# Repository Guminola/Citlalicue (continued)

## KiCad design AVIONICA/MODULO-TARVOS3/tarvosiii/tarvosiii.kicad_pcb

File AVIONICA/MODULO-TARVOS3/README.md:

# Modulo Tarvos-iii
2/3

modulo de comunicaciones Tarvos-iii

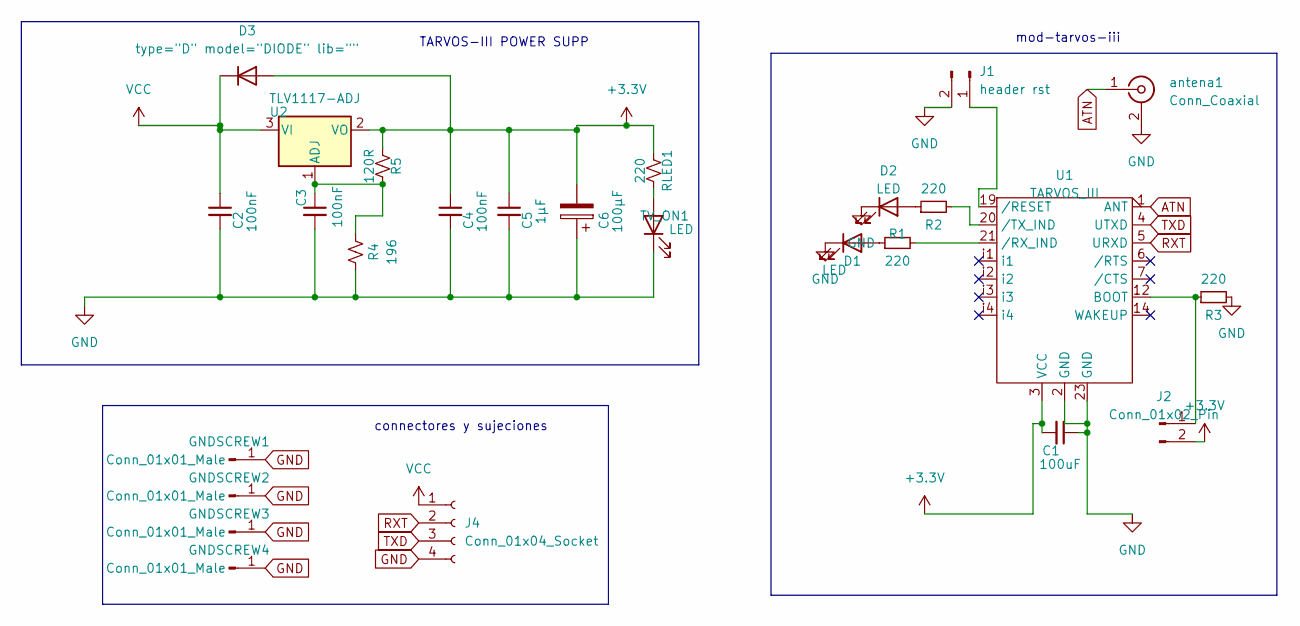
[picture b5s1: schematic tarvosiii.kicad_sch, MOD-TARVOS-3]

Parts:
C1: 100uF; C_0805_2012Metric_Pad1.18x1.45mm_HandSolder
C2, C3, C4: 100nF; C_0805_2012Metric_Pad1.18x1.45mm_HandSolder
C5: 1μF; C_0805_2012Metric_Pad1.18x1.45mm_HandSolder
C6: 100μF; CP_EIA-2012-12_Kemet-R
D1, D2: LED; LED_0805_2012Metric
D3: type="D" model="DIODE" lib=""; D_0805_2012Metric
GNDSCREW1, GNDSCREW2, GNDSCREW3, GNDSCREW4: Conn_01x01_Male; MountingHole_2.2mm_M2_Pad_Via
J1: header rst; PinHeader_1x02_P2.54mm_Vertical
J2: Conn_01x02_Pin; PinHeader_1x02_P2.54mm_Vertical
J4: Conn_01x04_Socket; JST_EH_S4B-EH_1x04_P2.50mm_Horizontal
R1, R2, R3: 220; R_0805_2012Metric_Pad1.20x1.40mm_HandSolder
R4: 196; R_0805_2012Metric_Pad1.20x1.40mm_HandSolder
R5: 120R; R_0805_2012Metric_Pad1.20x1.40mm_HandSolder
RLED1: 220; R_0805_2012Metric_Pad1.20x1.40mm_HandSolder
TV_ON1: LED; LED_0805_2012Metric
U1: TARVOS_III; tarvos-iii
U2: TLV1117-ADJ; SOT-223
antena1: Conn_Coaxial; SMA_Wurth_60312002114503_Vertical

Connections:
+3.3V: C1.2, C4.1, C5.1, C6.2, D3.1 (A), J2.2, R5.2, RLED1.2, U1.3 (VCC), U2.2 (VO)
ATN: U1.1 (ANT), antena1.1 (In)
GND: C1.1, C2.2, C3.2, C4.2, C5.2, C6.1, D1.1 (K), D2.1 (K), GNDSCREW1.1, GNDSCREW2.1, GNDSCREW3.1, GNDSCREW4.1, J1.2, J4.4, R3.2, R4.1, TV_ON1.1 (K), U1.2 (GND), U1.23 (GND), antena1.2 (Ext)
unnamed: D1.2 (A), R1.1
unnamed: D2.2 (A), R2.1
unnamed: J1.1, U1.19 (/RESET)
unnamed: J2.1, R3.1, U1.12 (BOOT)
unnamed: RLED1.1, TV_ON1.2 (A)
unnamed: R1.2, U1.21 (/RX_IND)
unnamed: R2.2, U1.20 (/TX_IND)
unnamed: C3.1, R4.2, R5.1, U2.1 (ADJ)
RXT: J4.2, U1.5 (URXD)
TXD: J4.3, U1.4 (UTXD)
VCC: C2.1, D3.2 (K), J4.1, U2.3 (VI)

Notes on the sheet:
TARVOS-III POWER SUPP
connectores y sujeciones
mod-tarvos-iii

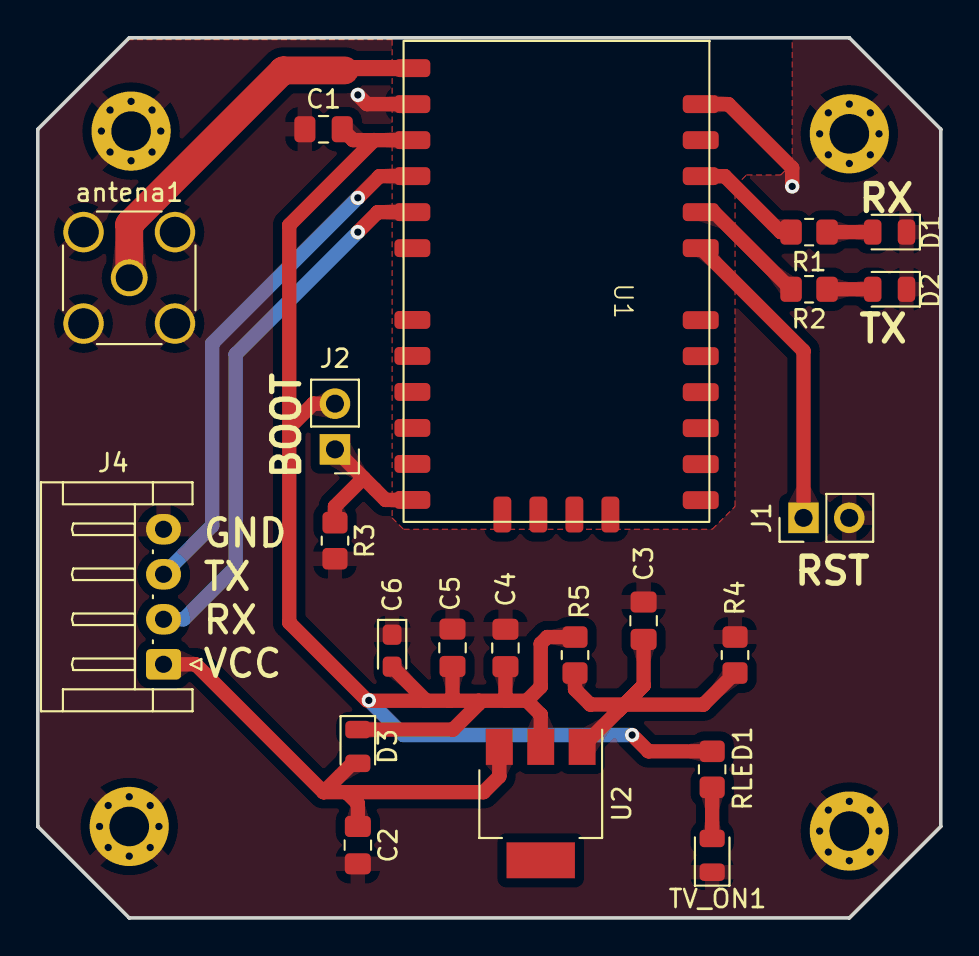
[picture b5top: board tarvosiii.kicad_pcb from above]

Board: 2 copper layers, 50.2 x 48.9 mm, 27 parts (1 on the bottom side), 14 nets.

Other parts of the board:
G2: LOGO; SPACE

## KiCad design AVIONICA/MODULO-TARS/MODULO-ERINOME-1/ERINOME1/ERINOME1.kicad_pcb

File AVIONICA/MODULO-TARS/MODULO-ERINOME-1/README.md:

# Modulo GPS Erinome-1
1/3
modulo del sistema gps con sistema Erinome-1

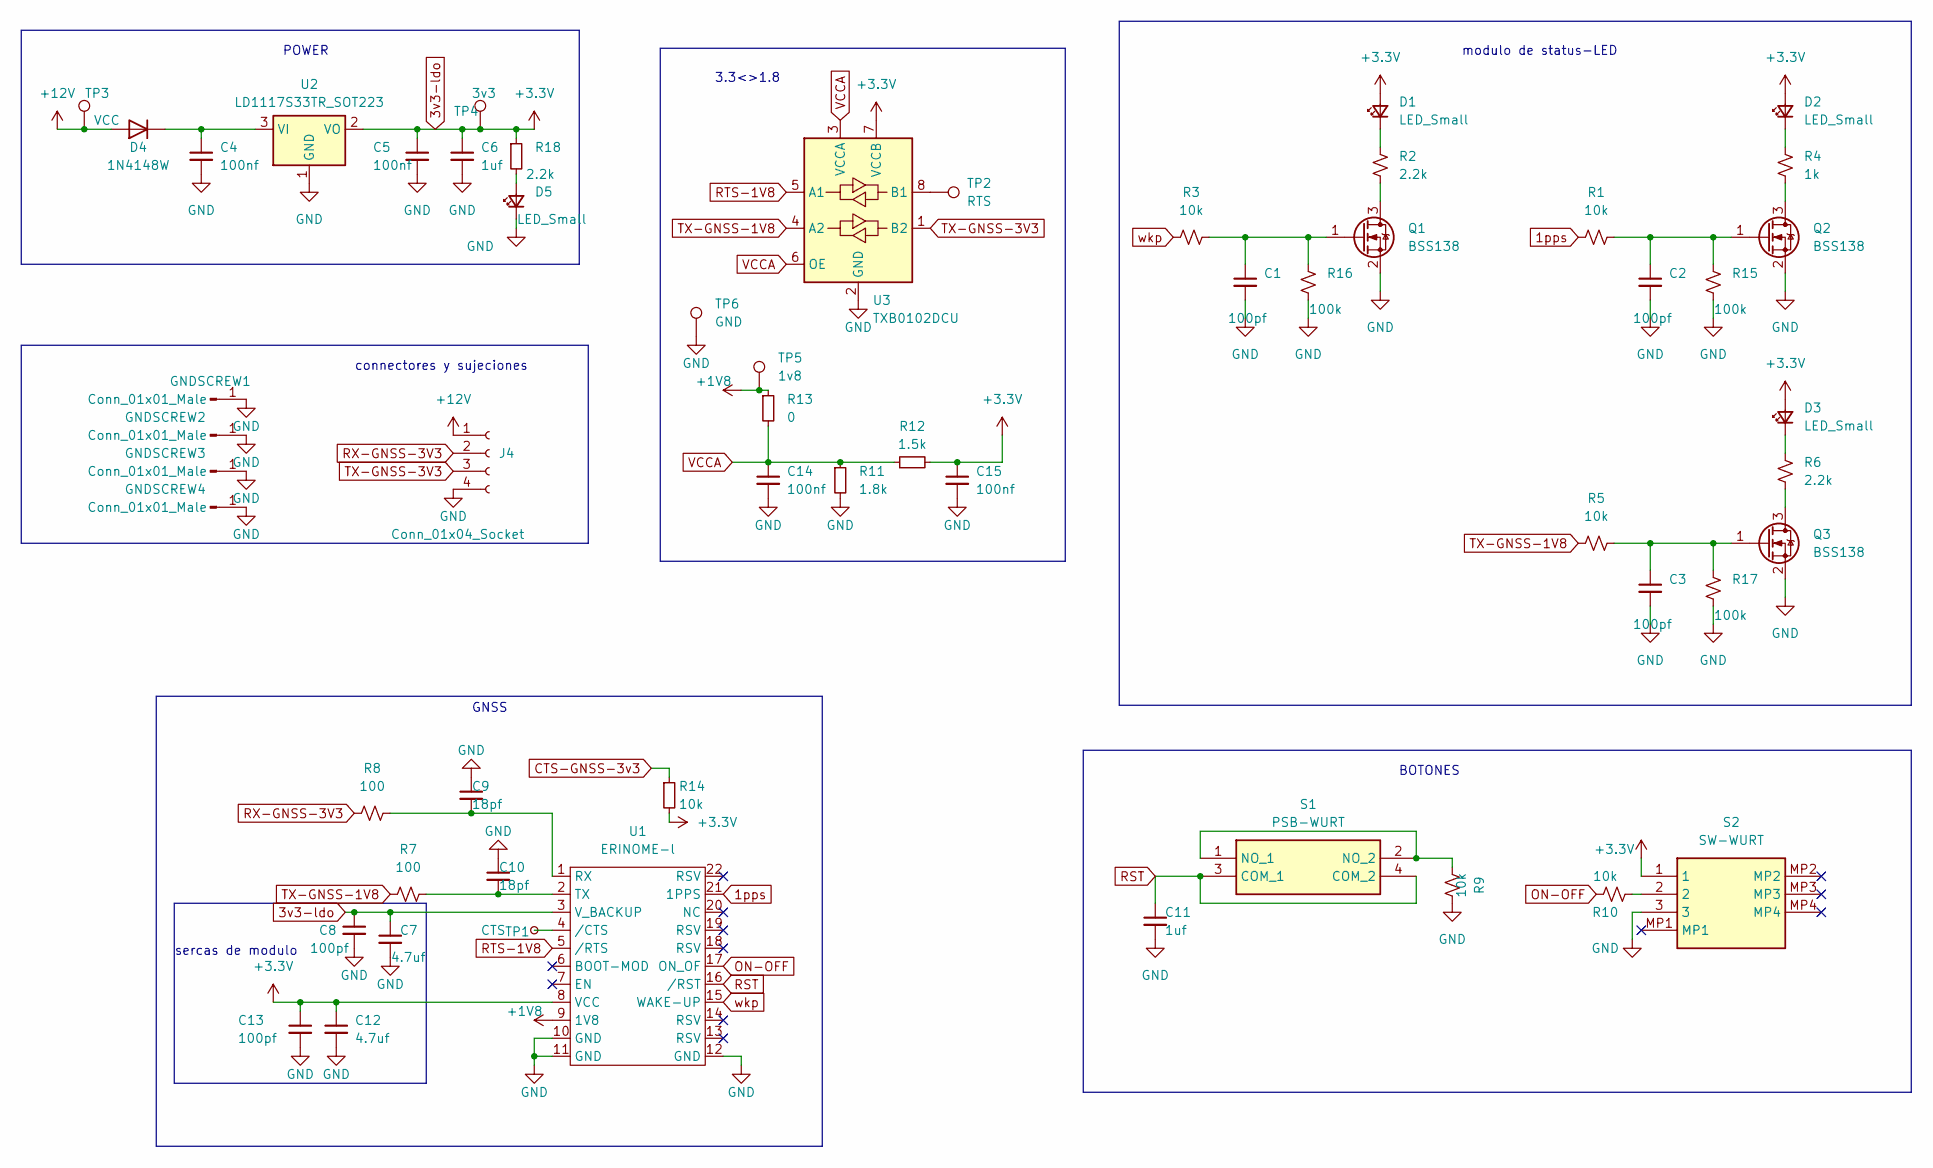
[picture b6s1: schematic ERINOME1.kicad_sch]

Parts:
C1, C2, C3, C8, C13: 100pf; C_0805_2012Metric_Pad1.18x1.45mm_HandSolder
C4, C5, C14, C15: 100nf; C_0805_2012Metric_Pad1.18x1.45mm_HandSolder
C6, C11: 1uf; C_0805_2012Metric_Pad1.18x1.45mm_HandSolder
C7, C12: 4.7uf; C_0805_2012Metric_Pad1.18x1.45mm_HandSolder
C9, C10: 18pf; C_0805_2012Metric_Pad1.18x1.45mm_HandSolder
D1, D2, D3, D5: LED_Small; LED_0805_2012Metric_Pad1.15x1.40mm_HandSolder
D4: 1N4148W; D_SOD-123
GNDSCREW1, GNDSCREW2, GNDSCREW3, GNDSCREW4: Conn_01x01_Male; MountingHole_2.2mm_M2_Pad_Via
J4: Conn_01x04_Socket; JST_EH_S4B-EH_1x04_P2.50mm_Horizontal
Q1, Q2, Q3: BSS138; SOT-23
R1, R3, R5, R9, R10, R14: 10k; R_0805_2012Metric_Pad1.20x1.40mm_HandSolder
R2, R6, R18: 2.2k; R_0805_2012Metric_Pad1.20x1.40mm_HandSolder
R4: 1k; R_0805_2012Metric_Pad1.20x1.40mm_HandSolder
R7, R8: 100; R_0805_2012Metric_Pad1.20x1.40mm_HandSolder
R11: 1.8k; R_0805_2012Metric_Pad1.20x1.40mm_HandSolder
R12: 1.5k; R_0805_2012Metric_Pad1.20x1.40mm_HandSolder
R13: 0; R_0805_2012Metric_Pad1.20x1.40mm_HandSolder
R15, R16, R17: 100k; R_0805_2012Metric_Pad1.20x1.40mm_HandSolder
S1: PSB-WURT; Mouser Part Number 710-430471031826
S2: SW-WURT; Mouser Part Number 710-450404015514
TP1: CTS; TestPoint_Pad_D2.0mm
TP2: RTS; TestPoint_Pad_D2.0mm
TP3: VCC; TestPoint_Pad_D2.0mm
TP4: 3v3; TestPoint_Pad_D2.0mm
TP5: 1v8; TestPoint_Pad_D2.0mm
TP6: GND; TestPoint_Pad_D2.0mm
U1: ERINOME-l; Erinome-l
U2: LD1117S33TR_SOT223; SOT-223-3_TabPin2
U3: TXB0102DCU; VSSOP-8_2.4x2.1mm_P0.5mm

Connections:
1pps: R1.1, U1.21 (1PPS)
3v3-ldo: C5.1, C6.1, C7.1, C8.1, C12.1, C13.1, C15.1, D1.2 (A), D2.2 (A), D3.2 (A), R12.2, R14.2, R18.1, S2.1, TP4.1, U1.3 (V_BACKUP), U1.8 (VCC), U2.2 (VO), U3.7 (VCCB)
+1V8: R13.1, TP5.1, U1.9 (1V8)
+12V: D4.2 (A), TP3.1; also elsewhere on the board
CTS-GNSS-3v3: R14.1
GND: C1.2, C2.2, C3.2, C4.2, C5.2, C6.2, C7.2, C8.2, C9.1, C10.1, C11.2, C12.2, C13.2, C14.2, C15.2, D5.1 (K), GNDSCREW1.1, GNDSCREW2.1, GNDSCREW3.1, GNDSCREW4.1, Q1.2 (S), Q2.2 (S), Q3.2 (S), R9.2, R11.2, R15.2, R16.2, R17.2, S2.3, TP6.1, U1.10 (GND), U1.11 (GND), U1.12 (GND), U2.1 (GND), U3.2 (GND); also elsewhere on the board
unnamed: D1.1 (K), R2.1
unnamed: D2.1 (K), R4.1
unnamed: D3.1 (K), R6.1
unnamed: C4.1, D4.1 (K), U2.3 (VI)
unnamed: D5.2 (A), R18.2
unnamed: Q1.3 (D), R2.2
unnamed: C1.1, Q1.1 (G), R3.2, R16.1
unnamed: Q2.3 (D), R4.2
unnamed: C2.1, Q2.1 (G), R1.2, R15.1
unnamed: Q3.3 (D), R6.2
unnamed: C3.1, Q3.1 (G), R5.2, R17.1
unnamed: R10.1, S2.2
unnamed: R9.1, S1.1 (NO_1), S1.2 (NO_2)
unnamed: C9.2, R8.2, U1.1 (RX)
unnamed: C10.2, R7.2, U1.2 (TX)
unnamed: TP1.1, U1.4 (/CTS)
unnamed: TP2.1, U3.8 (B1)
ON-OFF: R10.2, U1.17 (ON_OF)
RST: C11.1, S1.3 (COM_1), S1.4 (COM_2), U1.16 (/RST)
RTS-1V8: U1.5 (/RTS), U3.5 (A1)
RX-GNSS-3V3: R8.1; also elsewhere on the board
TX-GNSS-1V8: R5.1, R7.1, U3.4 (A2)
TX-GNSS-3V3: U3.1 (B2); also elsewhere on the board
VCCA: C14.1, R11.1, R12.1, R13.2, U3.3 (VCCA), U3.6 (OE)
wkp: R3.1, U1.15 (WAKE-UP)

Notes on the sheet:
BOTONES
modulo de status-LED
POWER
sercas de modulo
3.3<>1.8
GNSS
connectores y sujeciones

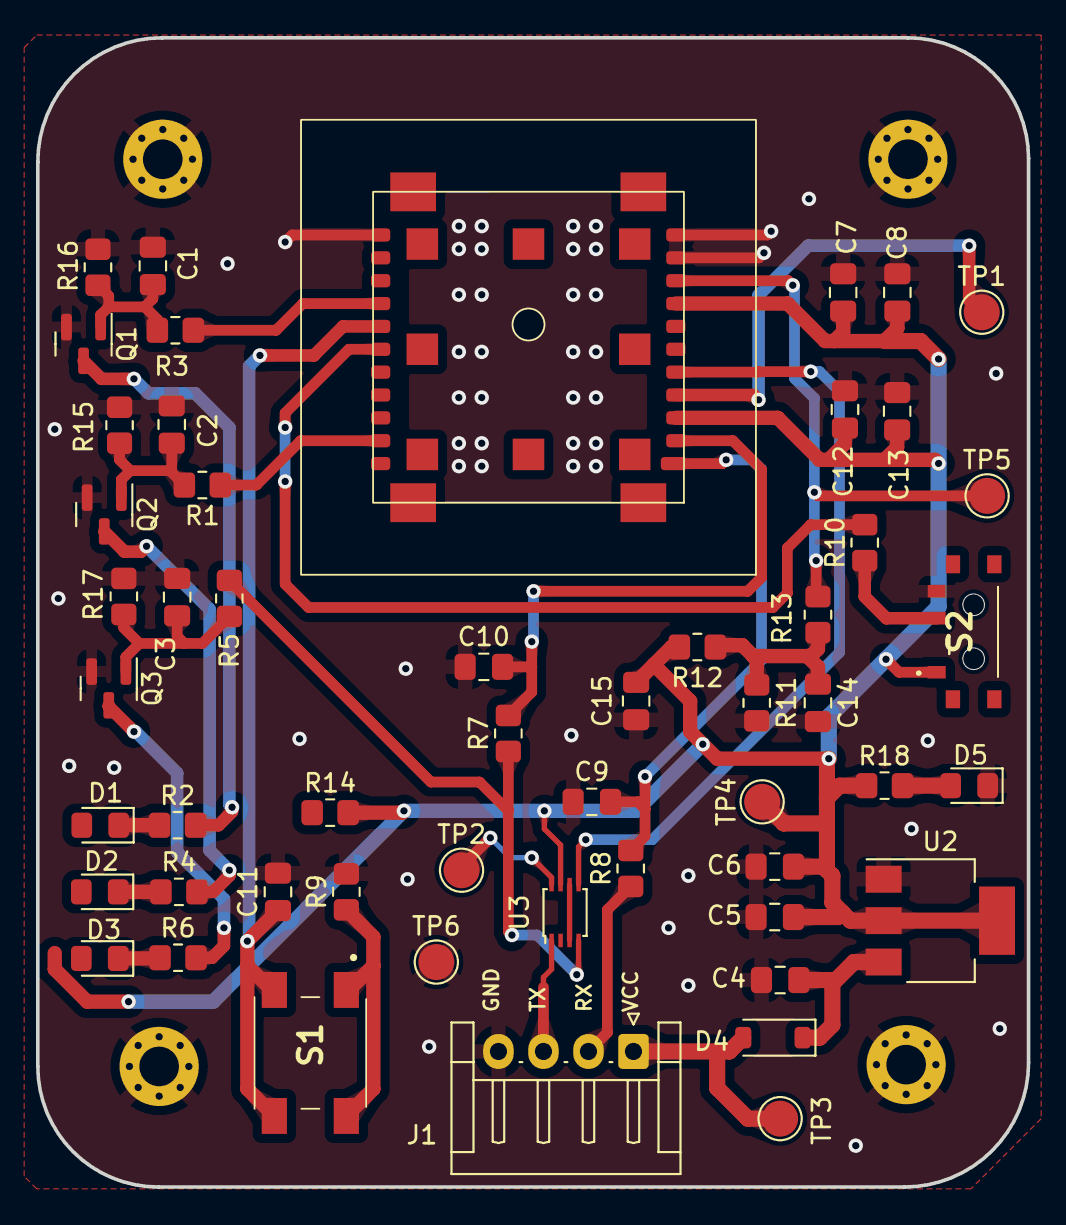
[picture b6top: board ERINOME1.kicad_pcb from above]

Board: 2 copper layers, 55.0 x 63.8 mm, 57 parts (0 on the bottom side), 30 nets.

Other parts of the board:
J1: Conn_01x04_Socket; JST_EH_S4B-EH_1x04_P2.50mm_Horizontal

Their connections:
+12V: J1.1; also elsewhere on the board
GND: J1.4; also elsewhere on the board
RX-GNSS-3V3: J1.2; also elsewhere on the board
TX-GNSS-3V3: J1.3; also elsewhere on the board

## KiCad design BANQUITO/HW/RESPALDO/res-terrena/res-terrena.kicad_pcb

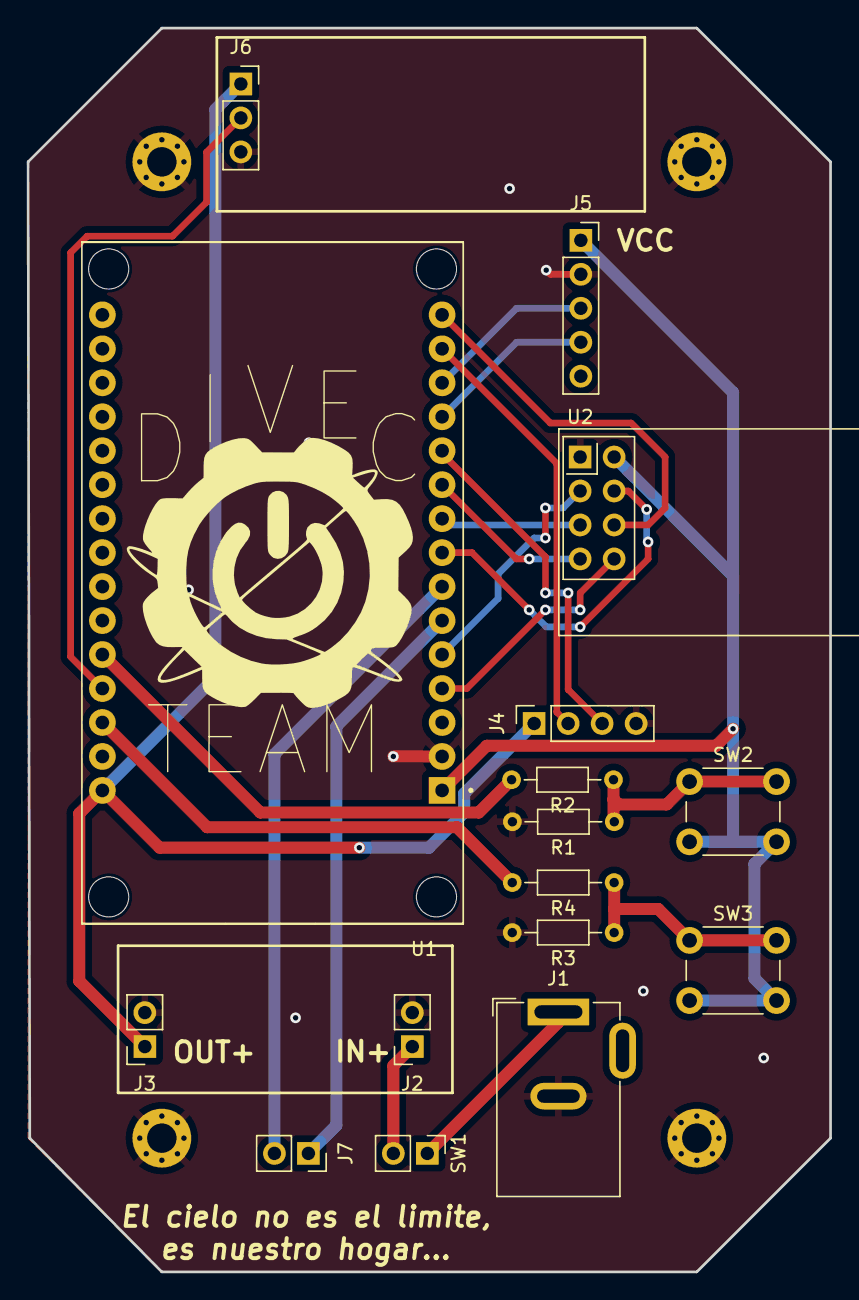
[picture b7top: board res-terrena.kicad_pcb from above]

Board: 2 copper layers, 60.0 x 93.0 mm, 22 parts (1 on the bottom side), 22 nets.

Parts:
G1: LOGO; DIVEC_LOGO
G2: LOGO; SPACE
GNDSCREW1, GNDSCREW2, GNDSCREW3, GNDSCREW4: Conn_01x01_Male; MountingHole_2.2mm_M2_Pad_Via
J1: Jack-DC; BarrelJack_GCT_DCJ200-10-A_Horizontal
J2, J3, J7: Conn_01x02_Socket; PinSocket_1x02_P2.54mm_Vertical
J4: Conn_01x04_Socket; PinSocket_1x04_P2.54mm_Vertical
J5: Conn_01x05_Socket; PinSocket_1x05_P2.54mm_Vertical
J6: Conn_01x03_Socket; PinSocket_1x03_P2.54mm_Vertical
R1, R2, R3, R4: 10k; R_Axial_DIN0204_L3.6mm_D1.6mm_P7.62mm_Horizontal
SW1: SW_DIP_x01; PinHeader_1x02_P2.54mm_Vertical
SW2, SW3: SW_Push; SW_PUSH_6mm_H5mm
U1: ESP32-DEVKIT-V1; MODULE_ESP32_DEVKIT_V1
U2: NRF24L01_Breakout; nRF24L01_Breakout

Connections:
3.3: J5.1, SW2.2, SW3.2, U1.1 (3V3), U2.2 (VCC)
BTT1: R2.2, U1.26 (D14)
BTT2: R4.2, U1.28 (D13)
CE: U1.5 (D4), U2.3 (CE)
CLK: U1.9 (D18), U2.5 (SCK)
CS: U1.8 (D5), U2.4 (~CSN)
GND: GNDSCREW1.1, GNDSCREW2.1, GNDSCREW3.1, GNDSCREW4.1, J1.2, J2.2, J3.2, J4.4, J5.2, J6.3, R1.2, R3.2, U1.2 (GND), U2.1 (GND)
IRQ: U1.4 (D2), U2.8 (IRQ)
MISO: U1.10 (D19), U2.7 (MISO)
MOSI: U1.15 (D23), U2.6 (MOSI)
unnamed: J1.1, SW1.1
unnamed: R1.1, R2.1, SW2.1
unnamed: R3.1, R4.1, SW3.1
RX: J5.4, U1.12 (RX0)
RX2: J7.1, U1.6 (RX2)
SCL: J4.2, U1.14 (D22)
SDA: J4.3, U1.11 (D21)
TX: J5.3, U1.13 (TX0)
TX2: J7.2, U1.7 (TX2)
VCC: J2.1, SW1.2
VIN: J3.1, J4.1, J6.1, U1.30 (VIN)
buzz: J6.2, U1.27 (D12)

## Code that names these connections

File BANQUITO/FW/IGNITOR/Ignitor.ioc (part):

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Mcu.Name=STM32H503RBTx
Mcu.Package=LQFP64
Mcu.UserName=STM32H503RBTx
PA10.Mode=Asynchronous
PA10.Signal=USART1_RX
PA13(JTMS/SWDIO).Mode=JTAG_4_pins
PA13(JTMS/SWDIO).Signal=DEBUG_JTMS-SWDIO
PA14(JTCK/SWCLK).Mode=JTAG_4_pins
PA14(JTCK/SWCLK).Signal=DEBUG_JTCK-SWCLK
PA15(JTDI).Mode=JTAG_4_pins
PA15(JTDI).Signal=DEBUG_JTDI
PA5.Signal=GPIO_Input
PA6.Signal=GPIO_Input
PA7.Mode=Audio_ClockInSAI1
PA7.Signal=AUDIOCLK
PA9.Mode=Asynchronous
PA9.Signal=USART1_TX
PB0.Mode=Asynchronous
PB0.Signal=USART2_TX
PB1.Mode=Asynchronous
PB1.Signal=USART2_RX
PB3(JTDO/TRACESWO).Mode=JTAG_4_pins
PB3(JTDO/TRACESWO).Signal=DEBUG_JTDO-SWO
PC0.Signal=GPIO_Input
PC1.Signal=GPIO_Input
PC10.Mode=Asynchronous
PC10.Signal=USART3_TX
PC11.Mode=Asynchronous
PC11.Signal=USART3_RX
PC14-OSC32_IN(OSC32_IN).Mode=LSE-External-Oscillator
PC14-OSC32_IN(OSC32_IN).Signal=RCC_OSC32_IN
PC15-OSC32_OUT(OSC32_OUT).Mode=LSE-External-Oscillator
PC15-OSC32_OUT(OSC32_OUT).Signal=RCC_OSC32_OUT
PC2.Signal=GPIO_Input
PC3.Signal=GPIO_Input
PC6.Signal=GPIO_Output
PC7.Signal=GPIO_Output
PC8.Signal=GPIO_Output
PC9.Signal=GPIO_Output
PH0-OSC_IN(PH0).Mode=HSE-External-Oscillator
PH0-OSC_IN(PH0).Signal=RCC_OSC_IN
PH1-OSC_OUT(PH1).Mode=HSE-External-Oscillator
PH1-OSC_OUT(PH1).Signal=RCC_OSC_OUT
RCC.HSE_VALUE=32000000
RCC.SYSCLKFreq_VALUE=64000000
board=custom

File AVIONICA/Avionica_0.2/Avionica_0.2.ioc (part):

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Mcu.Name=STM32H503RBTx
Mcu.Package=LQFP64
Mcu.UserName=STM32H503RBTx
PA10.Mode=Asynchronous
PA10.Signal=USART1_RX
PA13(JTMS/SWDIO).Mode=Serial_Wire
PA13(JTMS/SWDIO).Signal=DEBUG_JTMS-SWDIO
PA14(JTCK/SWCLK).Mode=Serial_Wire
PA14(JTCK/SWCLK).Signal=DEBUG_JTCK-SWCLK
PA8.GPIOParameters=GPIO_Label
PA8.GPIO_Label=MOSFET2
PA8.Signal=GPIO_Output
PA9.Mode=Asynchronous
PA9.Signal=USART1_TX
PB0.GPIOParameters=GPIO_Label
PB0.GPIO_Label=Tarvos_tx
PB0.Mode=Asynchronous
PB0.Signal=USART2_TX
PB1.GPIOParameters=GPIO_Label
PB1.GPIO_Label=Tarvos_rx
PB1.Mode=Asynchronous
PB1.Signal=USART2_RX
PB14.GPIOParameters=GPIO_Label
PB14.GPIO_Label=MOSFET1
PB14.Signal=GPIO_Output
PB15.GPIOParameters=GPIO_Label
PB15.GPIO_Label=EMRGNC
PB15.Signal=GPIO_Input
PB3(JTDO/TRACESWO).Mode=CRS SYNC Source GPIO
PB3(JTDO/TRACESWO).Signal=CRS_SYNC
PC0.Mode=Full_Duplex_Master
PC0.Signal=SPI1_SCK
PC1.Mode=NSS_Signal_Hard_Output
PC1.Signal=SPI1_NSS
PC10.GPIOParameters=GPIO_Label
PC10.GPIO_Label=USB_TX
PC10.Mode=Asynchronous
PC10.Signal=USART3_TX
PC11.GPIOParameters=GPIO_Label
PC11.GPIO_Label=USB_RX
PC11.Mode=Asynchronous
PC11.Signal=USART3_RX
PC2.Mode=Full_Duplex_Master
PC2.Signal=SPI1_MISO
PC3.Mode=Full_Duplex_Master
PC3.Signal=SPI1_MOSI
PC6.GPIOParameters=GPIO_Label
PC6.GPIO_Label=MOSFET3
PC6.Signal=GPIO_Output
PC7.GPIOParameters=GPIO_Label
PC7.GPIO_Label=MOSFET4
PC7.Signal=GPIO_Output
PC8.Mode=I2C
PC8.Signal=I2C1_SCL
PC9.Mode=I2C
PC9.Signal=I2C1_SDA
PH0-OSC_IN(PH0).Mode=HSE-External-Oscillator
PH0-OSC_IN(PH0).Signal=RCC_OSC_IN
PH1-OSC_OUT(PH1).Mode=HSE-External-Oscillator
PH1-OSC_OUT(PH1).Signal=RCC_OSC_OUT
RCC.HSE_VALUE=16000000
RCC.SYSCLKFreq_VALUE=72000000
RCC.SYSCLKSource=RCC_SYSCLKSOURCE_PLLCLK
board=custom

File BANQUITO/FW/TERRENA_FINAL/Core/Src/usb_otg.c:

/* USER CODE BEGIN Header */
/**
  ******************************************************************************
  * @file    usb_otg.c
  * @brief   This file provides code for the configuration
  *          of the USB_OTG instances.
  ******************************************************************************
  * @attention
  *
  * Copyright (c) 2024 STMicroelectronics.
  * All rights reserved.
  *
  * This software is licensed under terms that can be found in the LICENSE file
  * in the root directory of this software component.
  * If no LICENSE file comes with this software, it is provided AS-IS.
  *
  ******************************************************************************
  */
/* USER CODE END Header */
/* Includes ------------------------------------------------------------------*/
#include "usb_otg.h"

/* USER CODE BEGIN 0 */

/* USER CODE END 0 */

HCD_HandleTypeDef hhcd_USB_OTG_HS;

/* USB_OTG_HS init function */

void MX_USB_OTG_HS_HCD_Init(void)
{

  /* USER CODE BEGIN USB_OTG_HS_Init 0 */

  /* USER CODE END USB_OTG_HS_Init 0 */

  /* USER CODE BEGIN USB_OTG_HS_Init 1 */

  /* USER CODE END USB_OTG_HS_Init 1 */
  hhcd_USB_OTG_HS.Instance = USB_OTG_HS;
  hhcd_USB_OTG_HS.Init.Host_channels = 12;
  hhcd_USB_OTG_HS.Init.speed = HCD_SPEED_FULL;
  hhcd_USB_OTG_HS.Init.dma_enable = DISABLE;
  hhcd_USB_OTG_HS.Init.phy_itface = USB_OTG_EMBEDDED_PHY;
  hhcd_USB_OTG_HS.Init.Sof_enable = DISABLE;
  hhcd_USB_OTG_HS.Init.low_power_enable = DISABLE;
  hhcd_USB_OTG_HS.Init.vbus_sensing_enable = DISABLE;
  hhcd_USB_OTG_HS.Init.use_external_vbus = DISABLE;
  if (HAL_HCD_Init(&hhcd_USB_OTG_HS) != HAL_OK)
  {
    Error_Handler();
  }
  /* USER CODE BEGIN USB_OTG_HS_Init 2 */

  /* USER CODE END USB_OTG_HS_Init 2 */

}

void HAL_HCD_MspInit(HCD_HandleTypeDef* hcdHandle)
{

  GPIO_InitTypeDef GPIO_InitStruct = {0};
  if(hcdHandle->Instance==USB_OTG_HS)
  {
  /* USER CODE BEGIN USB_OTG_HS_MspInit 0 */

  /* USER CODE END USB_OTG_HS_MspInit 0 */

    __HAL_RCC_GPIOB_CLK_ENABLE();
    /**USB_OTG_HS GPIO Configuration
    PB12     ------> USB_OTG_HS_ID
    PB13     ------> USB_OTG_HS_VBUS
    PB14     ------> USB_OTG_HS_DM
    PB15     ------> USB_OTG_HS_DP
    */
    GPIO_InitStruct.Pin = OTG_HS_ID_Pin|OTG_HS_DM_Pin|OTG_HS_DP_Pin;
    GPIO_InitStruct.Mode = GPIO_MODE_AF_PP;
    GPIO_InitStruct.Pull = GPIO_NOPULL;
    GPIO_InitStruct.Speed = GPIO_SPEED_FREQ_LOW;
    GPIO_InitStruct.Alternate = GPIO_AF12_OTG_HS_FS;
    HAL_GPIO_Init(GPIOB, &GPIO_InitStruct);

    GPIO_InitStruct.Pin = VBUS_HS_Pin;
    GPIO_InitStruct.Mode = GPIO_MODE_INPUT;
    GPIO_InitStruct.Pull = GPIO_NOPULL;
    HAL_GPIO_Init(VBUS_HS_GPIO_Port, &GPIO_InitStruct);

    /* USB_OTG_HS clock enable */
    __HAL_RCC_USB_OTG_HS_CLK_ENABLE();

    /* USB_OTG_HS interrupt Init */
    HAL_NVIC_SetPriority(OTG_HS_IRQn, 0, 0);
    HAL_NVIC_EnableIRQ(OTG_HS_IRQn);
  /* USER CODE BEGIN USB_OTG_HS_MspInit 1 */

  /* USER CODE END USB_OTG_HS_MspInit 1 */
  }
}

void HAL_HCD_MspDeInit(HCD_HandleTypeDef* hcdHandle)
{

  if(hcdHandle->Instance==USB_OTG_HS)
  {
  /* USER CODE BEGIN USB_OTG_HS_MspDeInit 0 */

  /* USER CODE END USB_OTG_HS_MspDeInit 0 */
    /* Peripheral clock disable */
    __HAL_RCC_USB_OTG_HS_CLK_DISABLE();

    /**USB_OTG_HS GPIO Configuration
    PB12     ------> USB_OTG_HS_ID
    PB13     ------> USB_OTG_HS_VBUS
    PB14     ------> USB_OTG_HS_DM
    PB15     ------> USB_OTG_HS_DP
    */
    HAL_GPIO_DeInit(GPIOB, OTG_HS_ID_Pin|VBUS_HS_Pin|OTG_HS_DM_Pin|OTG_HS_DP_Pin);

    /* USB_OTG_HS interrupt Deinit */
    HAL_NVIC_DisableIRQ(OTG_HS_IRQn);
  /* USER CODE BEGIN USB_OTG_HS_MspDeInit 1 */

  /* USER CODE END USB_OTG_HS_MspDeInit 1 */
  }
}

/* USER CODE BEGIN 1 */

/* USER CODE END 1 */

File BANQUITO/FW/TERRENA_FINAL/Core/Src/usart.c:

/* USER CODE BEGIN Header */
/**
  ******************************************************************************
  * @file    usart.c
  * @brief   This file provides code for the configuration
  *          of the USART instances.
  ******************************************************************************
  * @attention
  *
  * Copyright (c) 2024 STMicroelectronics.
  * All rights reserved.
  *
  * This software is licensed under terms that can be found in the LICENSE file
  * in the root directory of this software component.
  * If no LICENSE file comes with this software, it is provided AS-IS.
  *
  ******************************************************************************
  */
/* USER CODE END Header */
/* Includes ------------------------------------------------------------------*/
#include "usart.h"

/* USER CODE BEGIN 0 */

/* USER CODE END 0 */

UART_HandleTypeDef huart5;
UART_HandleTypeDef huart1;

/* UART5 init function */
void MX_UART5_Init(void)
{

  /* USER CODE BEGIN UART5_Init 0 */

  /* USER CODE END UART5_Init 0 */

  /* USER CODE BEGIN UART5_Init 1 */

  /* USER CODE END UART5_Init 1 */
  huart5.Instance = UART5;
  huart5.Init.BaudRate = 115200;
  huart5.Init.WordLength = UART_WORDLENGTH_8B;
  huart5.Init.StopBits = UART_STOPBITS_1;
  huart5.Init.Parity = UART_PARITY_NONE;
  huart5.Init.Mode = UART_MODE_TX_RX;
  huart5.Init.HwFlowCtl = UART_HWCONTROL_NONE;
  huart5.Init.OverSampling = UART_OVERSAMPLING_16;
  if (HAL_UART_Init(&huart5) != HAL_OK)
  {
    Error_Handler();
  }
  /* USER CODE BEGIN UART5_Init 2 */

  /* USER CODE END UART5_Init 2 */

}
/* USART1 init function */

void MX_USART1_UART_Init(void)
{

  /* USER CODE BEGIN USART1_Init 0 */

  /* USER CODE END USART1_Init 0 */

  /* USER CODE BEGIN USART1_Init 1 */

  /* USER CODE END USART1_Init 1 */
  huart1.Instance = USART1;
  huart1.Init.BaudRate = 115200;
  huart1.Init.WordLength = UART_WORDLENGTH_8B;
  huart1.Init.StopBits = UART_STOPBITS_1;
  huart1.Init.Parity = UART_PARITY_NONE;
  huart1.Init.Mode = UART_MODE_TX_RX;
  huart1.Init.HwFlowCtl = UART_HWCONTROL_NONE;
  huart1.Init.OverSampling = UART_OVERSAMPLING_16;
  if (HAL_UART_Init(&huart1) != HAL_OK)
  {
    Error_Handler();
  }
  /* USER CODE BEGIN USART1_Init 2 */

  /* USER CODE END USART1_Init 2 */

}

void HAL_UART_MspInit(UART_HandleTypeDef* uartHandle)
{

  GPIO_InitTypeDef GPIO_InitStruct = {0};
  if(uartHandle->Instance==UART5)
  {
  /* USER CODE BEGIN UART5_MspInit 0 */

  /* USER CODE END UART5_MspInit 0 */
    /* UART5 clock enable */
    __HAL_RCC_UART5_CLK_ENABLE();

    __HAL_RCC_GPIOC_CLK_ENABLE();
    __HAL_RCC_GPIOD_CLK_ENABLE();
    /**UART5 GPIO Configuration
    PC12     ------> UART5_TX
    PD2     ------> UART5_RX
    */
    GPIO_InitStruct.Pin = GPIO_PIN_12;
    GPIO_InitStruct.Mode = GPIO_MODE_AF_PP;
    GPIO_InitStruct.Pull = GPIO_NOPULL;
    GPIO_InitStruct.Speed = GPIO_SPEED_FREQ_VERY_HIGH;
    GPIO_InitStruct.Alternate = GPIO_AF8_UART5;
    HAL_GPIO_Init(GPIOC, &GPIO_InitStruct);

    GPIO_InitStruct.Pin = GPIO_PIN_2;
    GPIO_InitStruct.Mode = GPIO_MODE_AF_PP;
    GPIO_InitStruct.Pull = GPIO_NOPULL;
    GPIO_InitStruct.Speed = GPIO_SPEED_FREQ_VERY_HIGH;
    GPIO_InitStruct.Alternate = GPIO_AF8_UART5;
    HAL_GPIO_Init(GPIOD, &GPIO_InitStruct);

    /* UART5 interrupt Init */
    HAL_NVIC_SetPriority(UART5_IRQn, 0, 0);
    HAL_NVIC_EnableIRQ(UART5_IRQn);
  /* USER CODE BEGIN UART5_MspInit 1 */

  /* USER CODE END UART5_MspInit 1 */
  }
  else if(uartHandle->Instance==USART1)
  {
  /* USER CODE BEGIN USART1_MspInit 0 */

  /* USER CODE END USART1_MspInit 0 */
    /* USART1 clock enable */
    __HAL_RCC_USART1_CLK_ENABLE();

    __HAL_RCC_GPIOA_CLK_ENABLE();
    /**USART1 GPIO Configuration
    PA9     ------> USART1_TX
    PA10     ------> USART1_RX
    */
    GPIO_InitStruct.Pin = STLINK_RX_Pin|STLINK_TX_Pin;
    GPIO_InitStruct.Mode = GPIO_MODE_AF_PP;
    GPIO_InitStruct.Pull = GPIO_NOPULL;
    GPIO_InitStruct.Speed = GPIO_SPEED_FREQ_VERY_HIGH;
    GPIO_InitStruct.Alternate = GPIO_AF7_USART1;
    HAL_GPIO_Init(GPIOA, &GPIO_InitStruct);

    /* USART1 interrupt Init */
    HAL_NVIC_SetPriority(USART1_IRQn, 0, 0);
    HAL_NVIC_EnableIRQ(USART1_IRQn);
  /* USER CODE BEGIN USART1_MspInit 1 */

  /* USER CODE END USART1_MspInit 1 */
  }
}

void HAL_UART_MspDeInit(UART_HandleTypeDef* uartHandle)
{

  if(uartHandle->Instance==UART5)
  {
  /* USER CODE BEGIN UART5_MspDeInit 0 */

  /* USER CODE END UART5_MspDeInit 0 */
    /* Peripheral clock disable */
    __HAL_RCC_UART5_CLK_DISABLE();

    /**UART5 GPIO Configuration
    PC12     ------> UART5_TX
    PD2     ------> UART5_RX
    */
    HAL_GPIO_DeInit(GPIOC, GPIO_PIN_12);

    HAL_GPIO_DeInit(GPIOD, GPIO_PIN_2);

    /* UART5 interrupt Deinit */
    HAL_NVIC_DisableIRQ(UART5_IRQn);
  /* USER CODE BEGIN UART5_MspDeInit 1 */

  /* USER CODE END UART5_MspDeInit 1 */
  }
  else if(uartHandle->Instance==USART1)
  {
  /* USER CODE BEGIN USART1_MspDeInit 0 */

  /* USER CODE END USART1_MspDeInit 0 */
    /* Peripheral clock disable */
    __HAL_RCC_USART1_CLK_DISABLE();

    /**USART1 GPIO Configuration
    PA9     ------> USART1_TX
    PA10     ------> USART1_RX
    */
    HAL_GPIO_DeInit(GPIOA, STLINK_RX_Pin|STLINK_TX_Pin);

    /* USART1 interrupt Deinit */
    HAL_NVIC_DisableIRQ(USART1_IRQn);
  /* USER CODE BEGIN USART1_MspDeInit 1 */

  /* USER CODE END USART1_MspDeInit 1 */
  }
}

/* USER CODE BEGIN 1 */

/* USER CODE END 1 */

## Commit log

2024-04-17 imported files from old repository
